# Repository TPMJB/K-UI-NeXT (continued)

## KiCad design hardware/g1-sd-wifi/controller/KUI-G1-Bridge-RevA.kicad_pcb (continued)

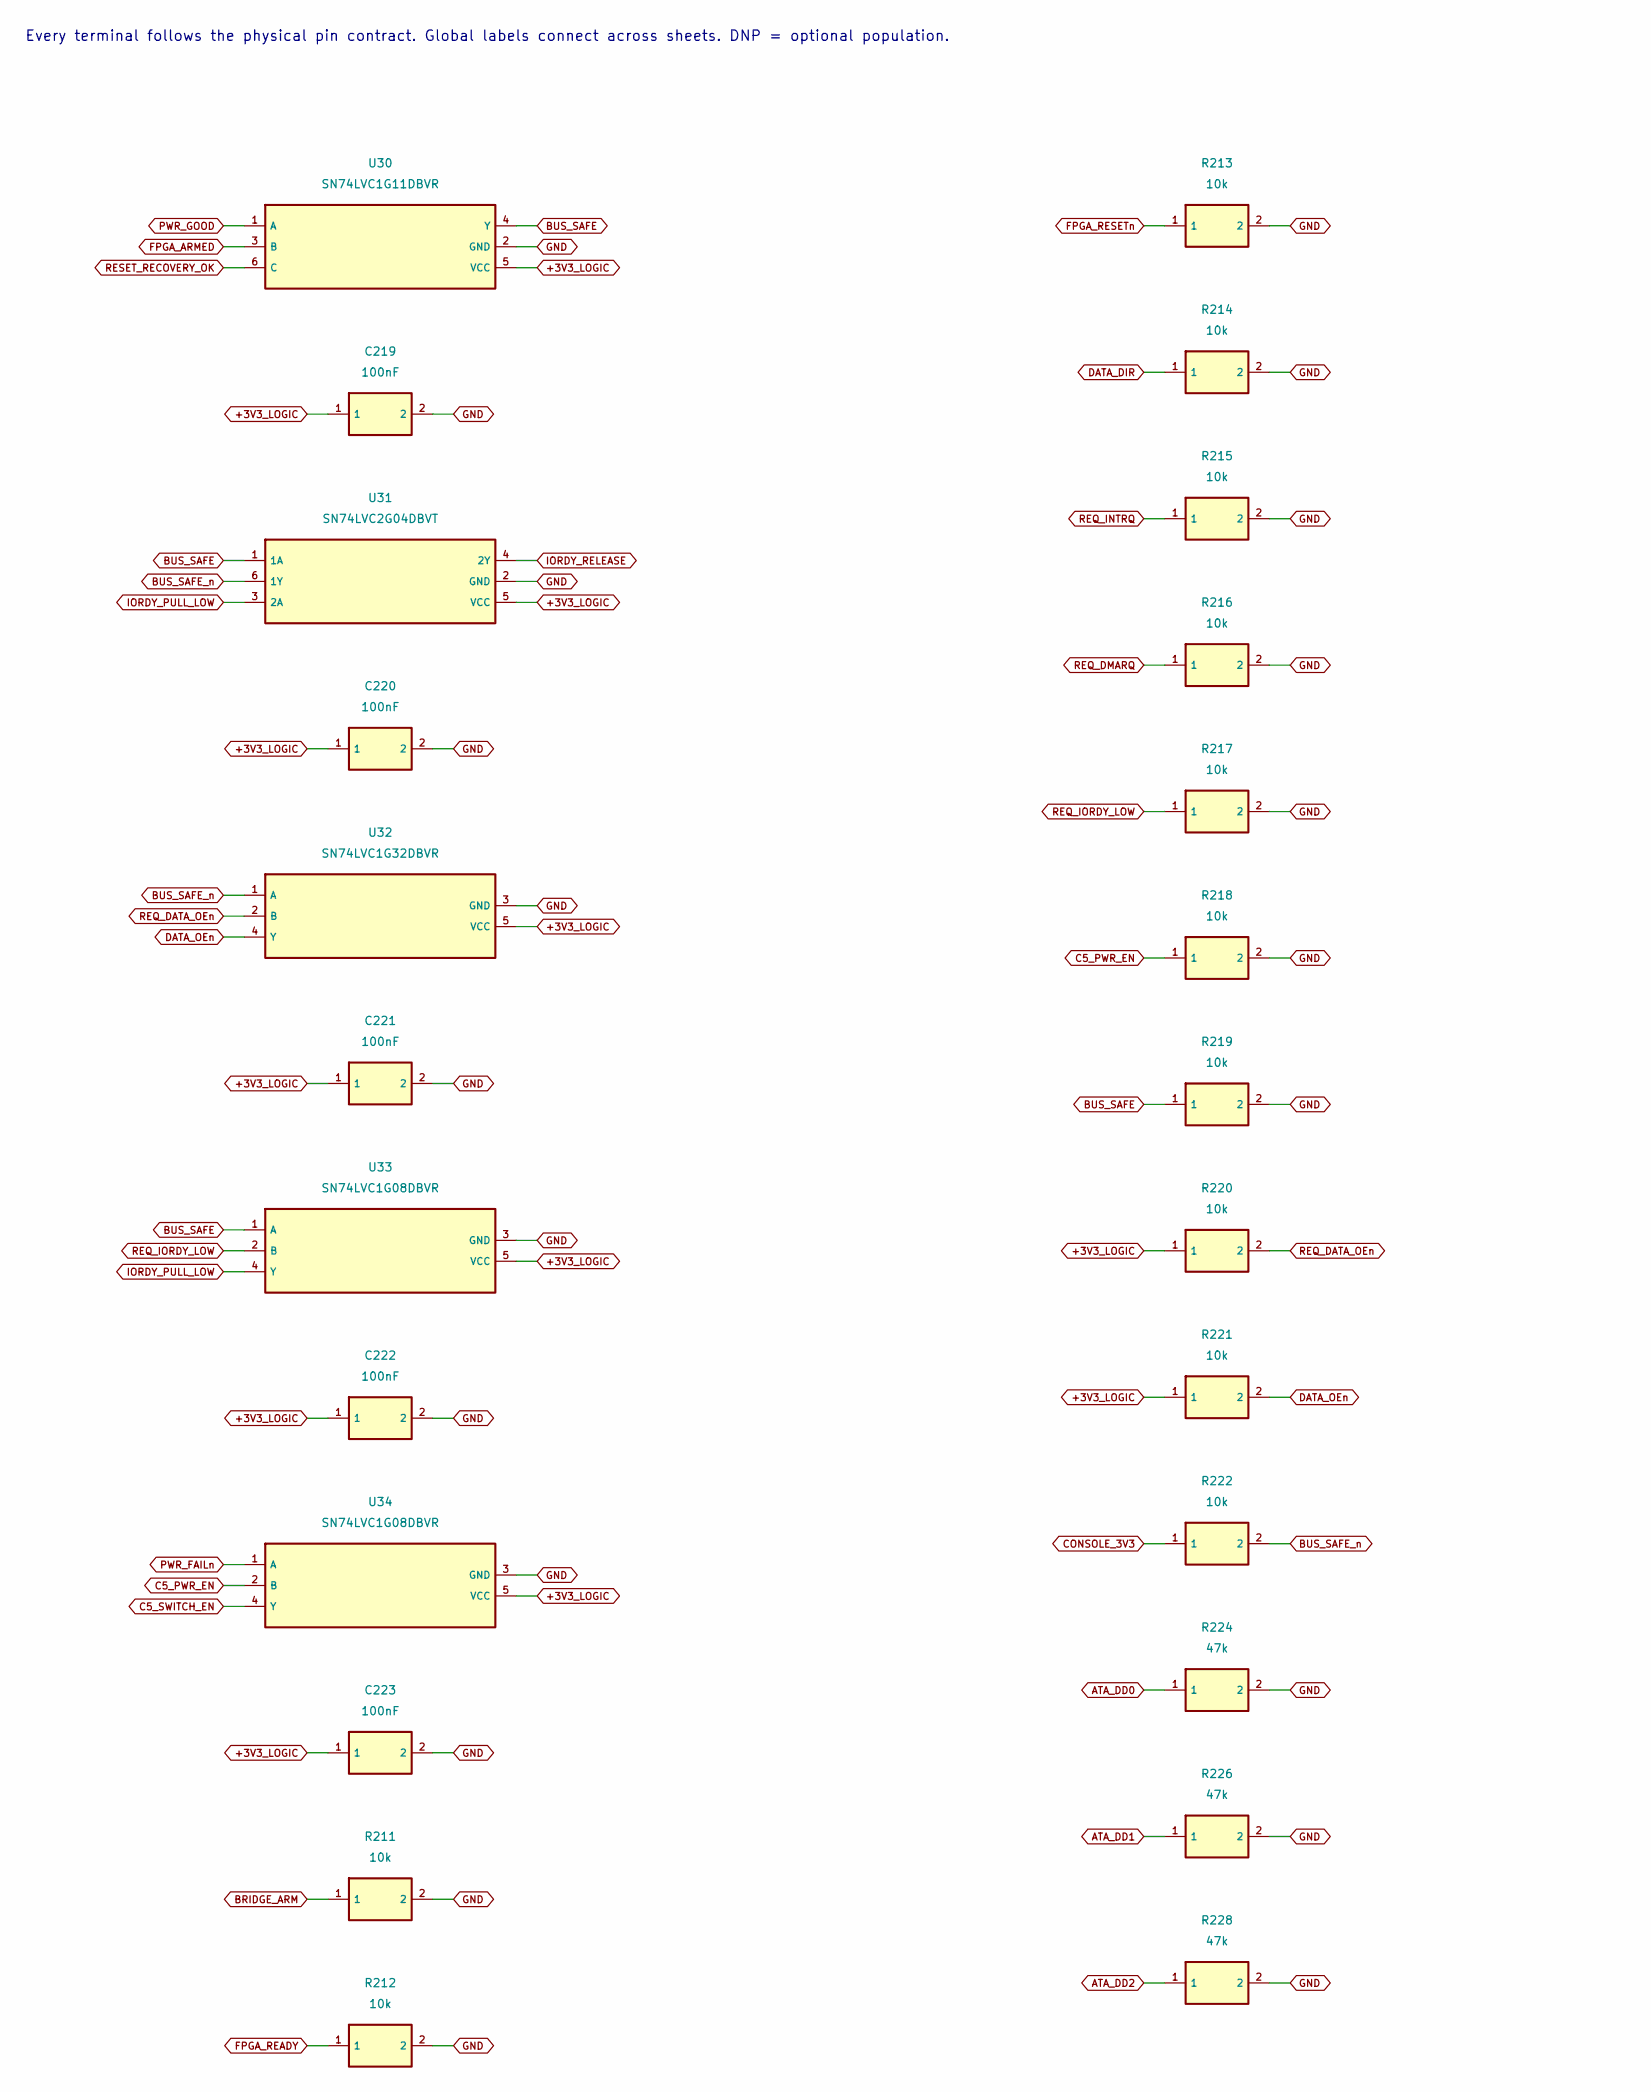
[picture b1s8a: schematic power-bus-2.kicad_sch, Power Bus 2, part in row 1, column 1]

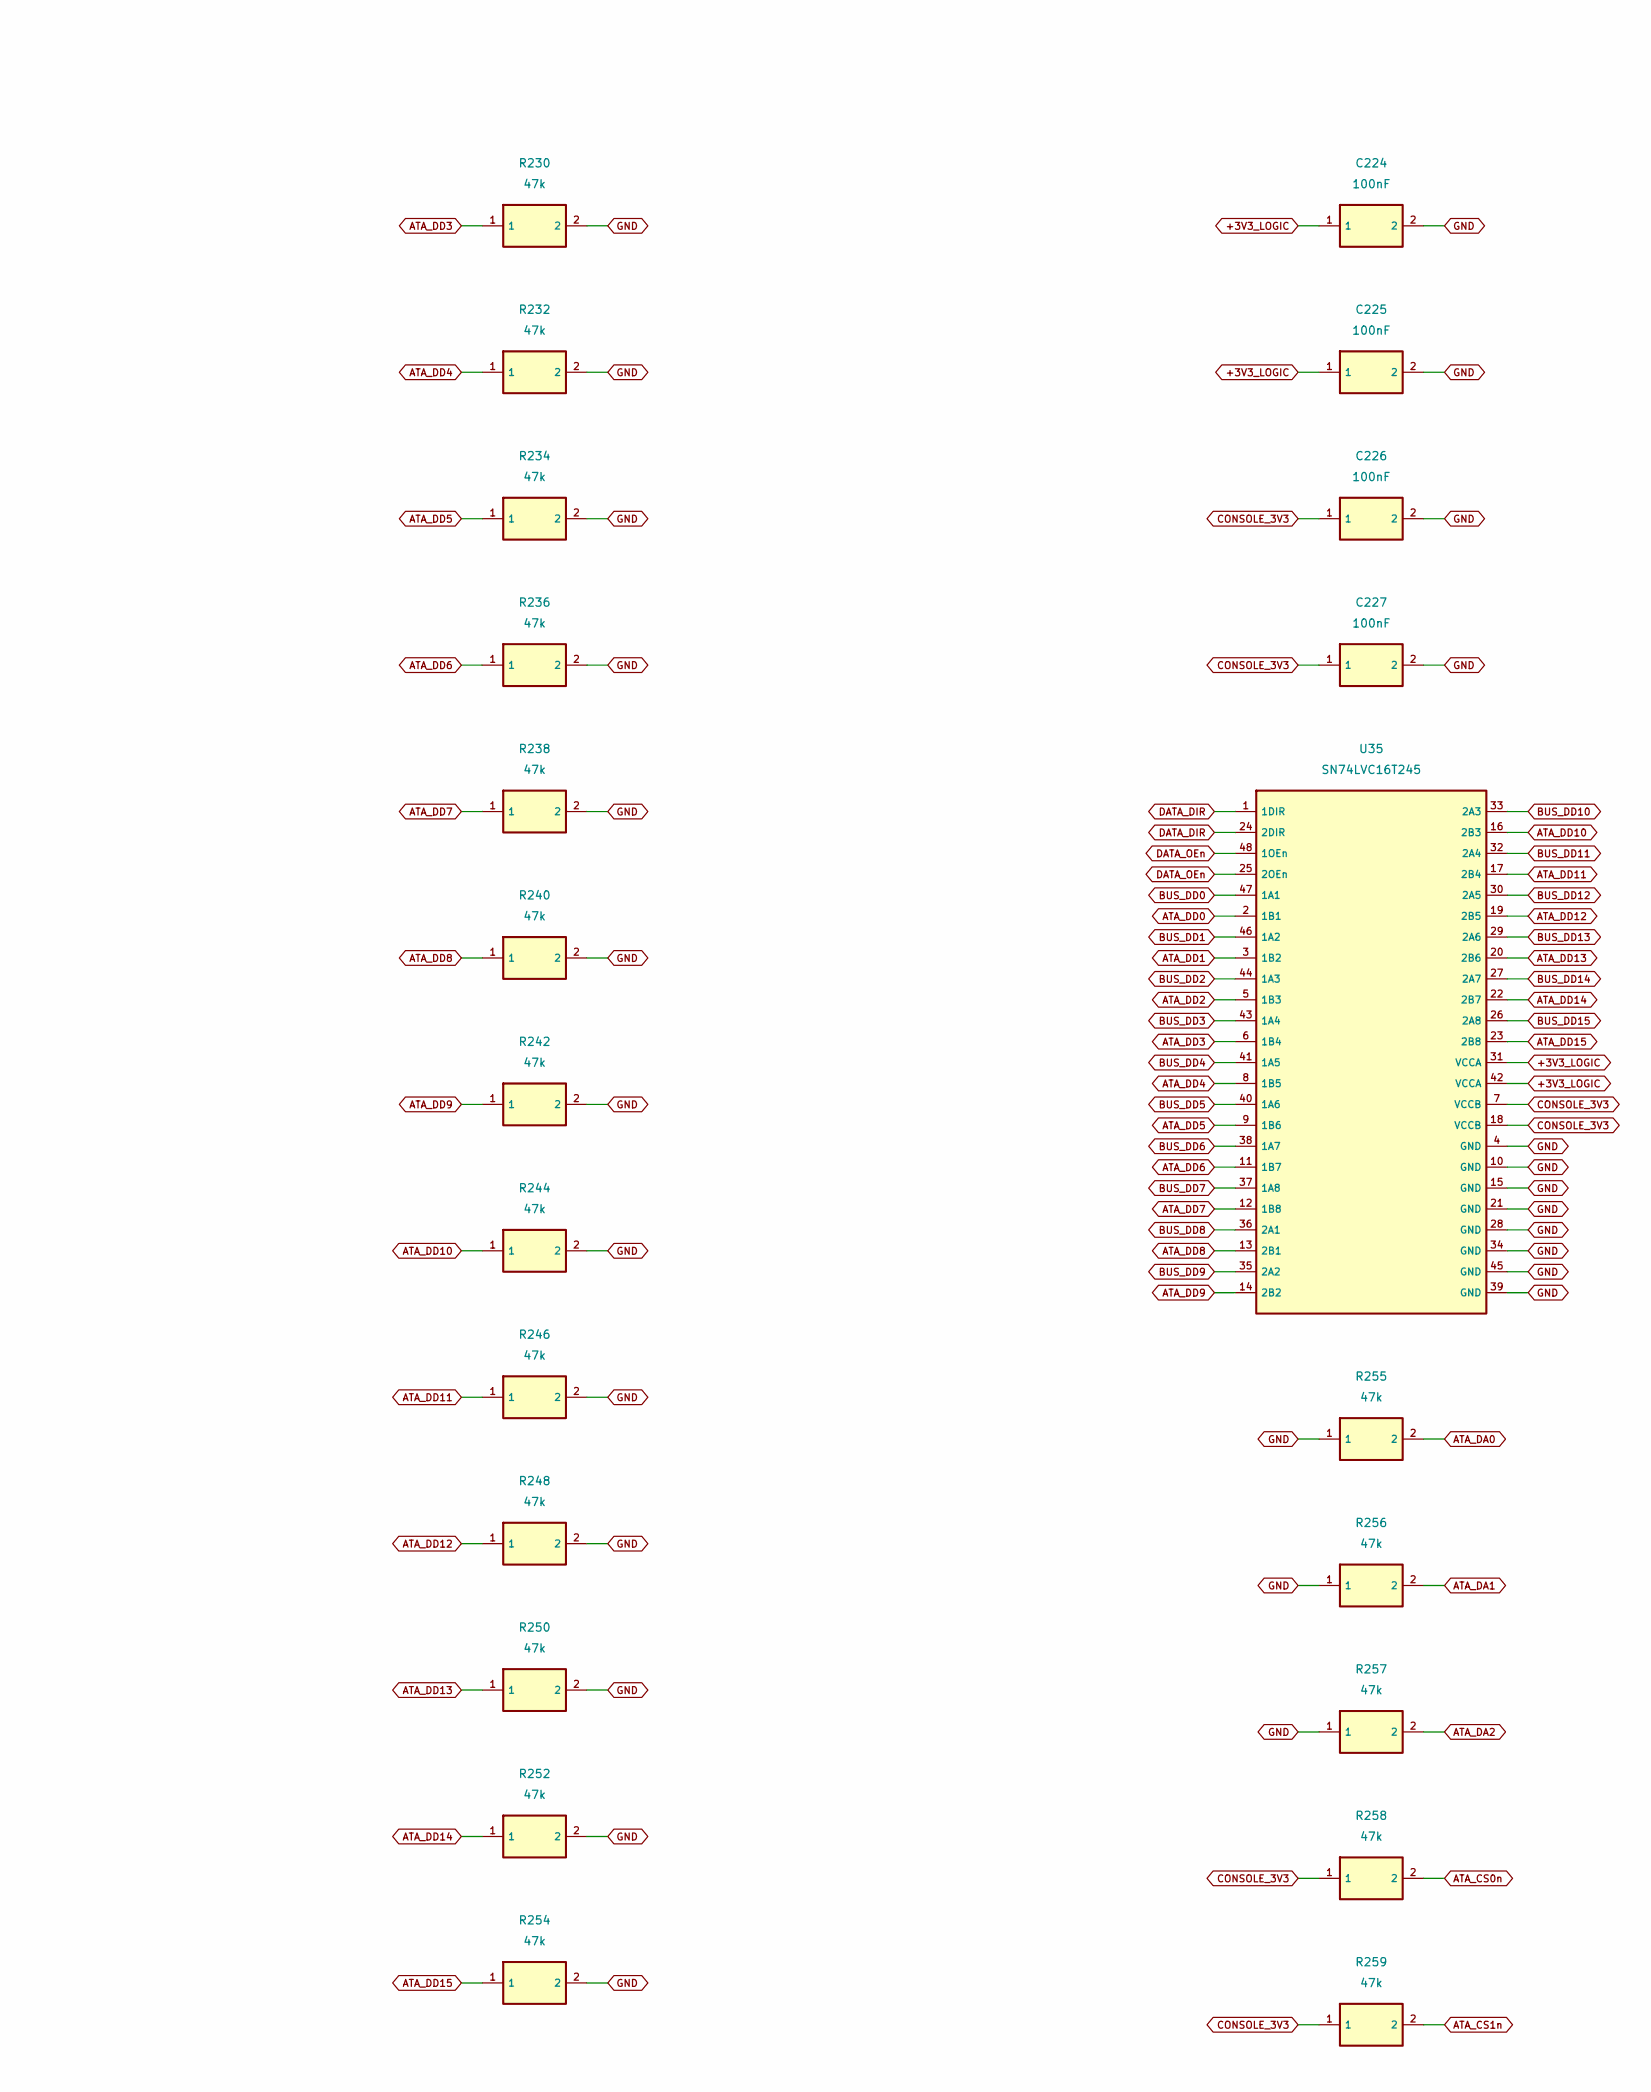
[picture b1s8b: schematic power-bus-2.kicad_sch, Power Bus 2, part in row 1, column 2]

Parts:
C219, C220, C221, C222, C223, C224, C225, C226, C227: 100nF; C_0402_1005Metric; MPN GRM155R71C104KA88D
R211, R212, R213, R214, R215, R216, R217, R218, R219, R220, R221, R222: 10k; R_0402_1005Metric; MPN RC0402FR-0710KL
R224, R226, R228, R230, R232, R234, R236, R238, R240, R242, R244, R246, R248, R250, R252, R254, R255, R256, R257, R258, R259: 47k; R_0402_1005Metric; MPN RC0402FR-0747KL
U30: SN74LVC1G11DBVR; SOT-23-6; MPN SN74LVC1G11DBVR
U31: SN74LVC2G04DBVT; SOT-23-6; MPN SN74LVC2G04DBVT; LCSC C2860342
U32: SN74LVC1G32DBVR; SOT-23-5; MPN SN74LVC1G32DBVR
U33, U34: SN74LVC1G08DBVR; SOT-23-5; MPN SN74LVC1G08DBVR
U35: SN74LVC16T245; TSSOP-48_6.1x12.5mm_P0.5mm; MPN SN74LVC16T245DGGR

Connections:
+3V3_LOGIC: C219.1, C220.1, C221.1, C222.1, C223.1, C224.1, C225.1, R220.1, R221.1, U30.5 (VCC), U31.5 (VCC), U32.5 (VCC), U33.5 (VCC), U34.5 (VCC), U35.31 (VCCA), U35.42 (VCCA); also elsewhere on the board
ATA_CS0n: R258.2; also elsewhere on the board
ATA_CS1n: R259.2; also elsewhere on the board
ATA_DA0: R255.2; also elsewhere on the board
ATA_DA1: R256.2; also elsewhere on the board
ATA_DA2: R257.2; also elsewhere on the board
ATA_DD0: R224.1, U35.2 (1B1); also elsewhere on the board
ATA_DD1: R226.1, U35.3 (1B2); also elsewhere on the board
ATA_DD2: R228.1, U35.5 (1B3); also elsewhere on the board
ATA_DD3: R230.1, U35.6 (1B4); also elsewhere on the board
ATA_DD4: R232.1, U35.8 (1B5); also elsewhere on the board
ATA_DD5: R234.1, U35.9 (1B6); also elsewhere on the board
ATA_DD6: R236.1, U35.11 (1B7); also elsewhere on the board
ATA_DD7: R238.1, U35.12 (1B8); also elsewhere on the board
ATA_DD8: R240.1, U35.13 (2B1); also elsewhere on the board
ATA_DD9: R242.1, U35.14 (2B2); also elsewhere on the board
ATA_DD10: R244.1, U35.16 (2B3); also elsewhere on the board
ATA_DD11: R246.1, U35.17 (2B4); also elsewhere on the board
ATA_DD12: R248.1, U35.19 (2B5); also elsewhere on the board
ATA_DD13: R250.1, U35.20 (2B6); also elsewhere on the board
ATA_DD14: R252.1, U35.22 (2B7); also elsewhere on the board
ATA_DD15: R254.1, U35.23 (2B8); also elsewhere on the board
BRIDGE_ARM: R211.1; also elsewhere on the board
BUS_DD0: U35.47 (1A1); also elsewhere on the board
BUS_DD1: U35.46 (1A2); also elsewhere on the board
BUS_DD2: U35.44 (1A3); also elsewhere on the board
BUS_DD3: U35.43 (1A4); also elsewhere on the board
BUS_DD4: U35.41 (1A5); also elsewhere on the board
BUS_DD5: U35.40 (1A6); also elsewhere on the board
BUS_DD6: U35.38 (1A7); also elsewhere on the board
BUS_DD7: U35.37 (1A8); also elsewhere on the board
BUS_DD8: U35.36 (2A1); also elsewhere on the board
BUS_DD9: U35.35 (2A2); also elsewhere on the board
BUS_DD10: U35.33 (2A3); also elsewhere on the board
BUS_DD11: U35.32 (2A4); also elsewhere on the board
BUS_DD12: U35.30 (2A5); also elsewhere on the board
BUS_DD13: U35.29 (2A6); also elsewhere on the board
BUS_DD14: U35.27 (2A7); also elsewhere on the board
BUS_DD15: U35.26 (2A8); also elsewhere on the board
BUS_SAFE: R219.1, U30.4 (Y), U31.1 (1A), U33.1 (A); also elsewhere on the board
BUS_SAFE_n: R222.2, U31.6 (1Y), U32.1 (A); also elsewhere on the board
C5_PWR_EN: R218.1, U34.2 (B); also elsewhere on the board
C5_SWITCH_EN: U34.4 (Y); also elsewhere on the board
CONSOLE_3V3: C226.1, C227.1, R222.1, R258.1, R259.1, U35.7 (VCCB), U35.18 (VCCB); also elsewhere on the board
DATA_DIR: R214.1, U35.1 (1DIR), U35.24 (2DIR); also elsewhere on the board
DATA_OEn: R221.2, U32.4 (Y), U35.25 (2OEn), U35.48 (1OEn); also elsewhere on the board
FPGA_ARMED: U30.3 (B); also elsewhere on the board
FPGA_READY: R212.1; also elsewhere on the board
FPGA_RESETn: R213.1; also elsewhere on the board
GND: C219.2, C220.2, C221.2, C222.2, C223.2, C224.2, C225.2, C226.2, C227.2, R211.2, R212.2, R213.2, R214.2, R215.2, R216.2, R217.2, R218.2, R219.2, R224.2, R226.2, R228.2, R230.2, R232.2, R234.2, R236.2, R238.2, R240.2, R242.2, R244.2, R246.2, R248.2, R250.2, R252.2, R254.2, R255.1, R256.1, R257.1, U30.2 (GND), U31.2 (GND), U32.3 (GND), U33.3 (GND), U34.3 (GND), U35.4 (GND), U35.10 (GND), U35.15 (GND), U35.21 (GND), U35.28 (GND), U35.34 (GND), U35.39 (GND), U35.45 (GND); also elsewhere on the board
IORDY_PULL_LOW: U31.3 (2A), U33.4 (Y)
IORDY_RELEASE: U31.4 (2Y); also elsewhere on the board
PWR_FAILn: U34.1 (A); also elsewhere on the board
PWR_GOOD: U30.1 (A); also elsewhere on the board
REQ_DATA_OEn: R220.2, U32.2 (B); also elsewhere on the board
REQ_DMARQ: R216.1; also elsewhere on the board
REQ_INTRQ: R215.1; also elsewhere on the board
REQ_IORDY_LOW: R217.1, U33.2 (B); also elsewhere on the board
RESET_RECOVERY_OK: U30.6 (C); also elsewhere on the board

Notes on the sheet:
Every terminal follows the physical pin contract. Global labels connect across sheets. DNP = optional population.

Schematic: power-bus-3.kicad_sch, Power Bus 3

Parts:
C228, C229, C230, C231, C232, C233, C234: 100nF; C_0402_1005Metric; MPN GRM155R71C104KA88D
C235, C236: 22uF; C_0805_2012Metric; MPN GRM21BR61A226ME51L
R260, R261, R262, R263: 47k; R_0402_1005Metric; MPN RC0402FR-0747KL
R264, R265, R266, R267, R268: 10k; R_0402_1005Metric; MPN RC0402FR-0710KL
R269: 100k; R_0402_1005Metric; MPN RC0402FR-07100KL
TP20: PWR_FAILn; TestPoint_Pad_D1.0mm; MPN PCB test point
TP21: PWR_GOOD; TestPoint_Pad_D1.0mm; MPN PCB test point
TP22: BUS_SAFE; TestPoint_Pad_D1.0mm; MPN PCB test point
TP23: DATA_OEn; TestPoint_Pad_D1.0mm; MPN PCB test point
TP24: +5V_HOLD; TestPoint_Pad_D1.0mm; MPN PCB test point
TP25: RESERVE_5V; TestPoint_Pad_D1.0mm; MPN PCB test point
TP26: CONSOLE_3V3; TestPoint_Pad_D1.0mm; MPN PCB test point
U36: SN74LVC244A host controls; TSSOP-20_4.4x6.5mm_P0.65mm; MPN SN74LVC244APWR
U37: SN74LVC1G17 host RESETn; SOT-23-5; MPN SN74LVC1G17DBVR
U38: SN74LVC1G125 qualified ATA_INTRQ; SOT-23-5; MPN SN74LVC1G125DBVR
U39: SN74LVC1G125 qualified ATA_DMARQ; SOT-23-5; MPN SN74LVC1G125DBVR
U70: SN74LVC1G07 open-drain IORDY; SOT-23-5; MPN SN74LVC1G07DBVR
U71: TPS22919 Wi-Fi input switch; SOT-363_SC-70-6; MPN TPS22919DCKR
U72, U73: SN74LVC1G32DBVR; SOT-23-5; MPN SN74LVC1G32DBVR

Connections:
+3V3_LOGIC: C228.1, C229.1, C230.1, C232.1, R264.1, R266.1, U36.20 (VCC), U37.5 (VCC), U72.5 (VCC), U73.5 (VCC); also elsewhere on the board
+5V_C5: C236.1, U71.5 (QOD), U71.6 (VOUT); also elsewhere on the board
+5V_HOLD: TP24.1; also elsewhere on the board
ATA_CS0n: U36.8 (1A4); also elsewhere on the board
ATA_CS1n: U36.11 (2A1); also elsewhere on the board
ATA_DA0: U36.2 (1A1); also elsewhere on the board
ATA_DA1: U36.4 (1A2); also elsewhere on the board
ATA_DA2: U36.6 (1A3); also elsewhere on the board
ATA_DIORn: R260.2, U36.13 (2A2); also elsewhere on the board
ATA_DIOWn: R261.2, U36.15 (2A3); also elsewhere on the board
ATA_DMACKn: R262.2, U36.17 (2A4); also elsewhere on the board
ATA_DMARQ: U39.4 (Y); also elsewhere on the board
ATA_INTRQ: U38.4 (Y); also elsewhere on the board
ATA_IORDY: U70.4 (Y); also elsewhere on the board
ATA_RESETn: R263.1, U37.2 (A); also elsewhere on the board
BUS_CS0n: U36.12 (1Y4); also elsewhere on the board
BUS_CS1n: U36.9 (2Y1); also elsewhere on the board
BUS_DA0: U36.18 (1Y1); also elsewhere on the board
BUS_DA1: U36.16 (1Y2); also elsewhere on the board
BUS_DA2: U36.14 (1Y3); also elsewhere on the board
BUS_DIORn: U36.7 (2Y2); also elsewhere on the board
BUS_DIOWn: U36.5 (2Y3); also elsewhere on the board
BUS_DMACKn: U36.3 (2Y4); also elsewhere on the board
BUS_RESETn: U37.4 (Y); also elsewhere on the board
BUS_SAFE: TP22.1; also elsewhere on the board
BUS_SAFE_n: U72.1 (A), U73.1 (A); also elsewhere on the board
C5_SWITCH_EN: R269.1, U71.3 (ON); also elsewhere on the board
CONSOLE_3V3: C231.1, C233.1, C234.1, R260.1, R261.1, R262.1, R265.1, R267.1, R268.1, TP26.1, U38.5 (VCC), U39.5 (VCC), U70.5 (VCC); also elsewhere on the board
DATA_OEn: TP23.1; also elsewhere on the board
DMARQ_OEn: R267.2, U39.1 (OEn), U73.4 (Y); also elsewhere on the board
GND: C228.2, C229.2, C230.2, C231.2, C232.2, C233.2, C234.2, C235.2, C236.2, R263.2, R269.2, U36.1 (1OEn), U36.10 (GND), U36.19 (2OEn), U37.3 (GND), U38.3 (GND), U39.3 (GND), U70.3 (GND), U71.2 (GND), U72.3 (GND), U73.3 (GND); also elsewhere on the board
INTRQ_OEn: R265.2, U38.1 (OEn), U72.4 (Y); also elsewhere on the board
IORDY_RELEASE: R268.2, U70.2 (A); also elsewhere on the board
PRIMARY_5V: C235.1, U71.1 (IN); also elsewhere on the board
PWR_FAILn: TP20.1; also elsewhere on the board
PWR_GOOD: TP21.1; also elsewhere on the board
REQ_DMARQ: U39.2 (A); also elsewhere on the board
REQ_DMARQ_OEn: R266.2, U73.2 (B); also elsewhere on the board
REQ_INTRQ: U38.2 (A); also elsewhere on the board
REQ_INTRQ_OEn: R264.2, U72.2 (B); also elsewhere on the board
RESERVE_5V: TP25.1; also elsewhere on the board

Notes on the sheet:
Every terminal follows the physical pin contract. Global labels connect across sheets. DNP = optional population.

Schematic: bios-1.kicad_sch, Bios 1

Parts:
C400, C402, C403, C404, C405, C406: 100nF; C_0603_1608Metric; MPN CC0603KRX7R9BB104; not fitted
C401: 4.7uF; C_0603_1608Metric; MPN GRM188R60J475KE19D; not fitted
J40: FH12-14S-0.5SH(55); Hirose_FH12-14S-0.5SH_1x14-1MP_P0.50mm_Horizontal; MPN FH12-14S-0.5SH(55); not fitted
J41: FH12-6S-0.5SH(55); Hirose_FH12-6S-0.5SH_1x06-1MP_P0.50mm_Horizontal; MPN FH12-6S-0.5SH(55); not fitted
JP40: PROGRAM ARM - normally OPEN; SolderJumper-2_P1.3mm_Open_RoundedPad1.0x1.5mm; MPN PCB_SOLDER_BRIDGE; not fitted
R400, R401, R402, R403, R404, R405, R406, R407, R408, R412, R413, R414: 10k; R_0603_1608Metric; MPN RC0603FR-0710KL; not fitted
R409: 10k; R_0603_1608Metric; MPN RC0603FR-0710KL
R410: 1k; R_0402_1005Metric; MPN RC0402FR-071KL
R411: 100k; R_0603_1608Metric; MPN RC0603FR-07100KL; not fitted
SW40: STOCK_RECOVERY / CUSTOM (OFFBOARD); MPN 7201SYZBE; not fitted
TP40: NOR_RY_BY; TestPoint_Pad_D1.0mm; MPN PCB_TEST_PAD; not fitted
U40: MX29LV640ETTI-70G x8 / 4 x 2MiB; TSOP-I-48_18.4x12mm_P0.5mm; MPN MX29LV640ETTI-70G; not fitted
U41: SN74LVC2G125 bank-domain buffer; SOT-23-8; MPN SN74LVC2G125DCTR; not fitted
U42: SN74LVC1G11 write-authorize AND; SOT-23-6; MPN SN74LVC1G11DBVR; not fitted
U43: SN74LVC1G04 write-block inverter; SOT-23-5; MPN SN74LVC1G04DBVR; not fitted
U44: SN74LVC1G332 NOR WE qualifier; SOT-23-6; MPN SN74LVC1G332DBVR; not fitted
U45: TLV803EB29 console-rail NOR reset; SOT-23; MPN TLV803EB29DBZR; not fitted

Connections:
ATA_DA0: U40.18 (A7); also elsewhere on the board
ATA_DA1: U40.8 (A8); also elsewhere on the board
ATA_DA2: U40.7 (A9); also elsewhere on the board
ATA_DD0: U40.29 (DQ0); also elsewhere on the board
ATA_DD1: U40.31 (DQ1); also elsewhere on the board
ATA_DD2: U40.33 (DQ2); also elsewhere on the board
ATA_DD3: U40.35 (DQ3); also elsewhere on the board
ATA_DD4: U40.38 (DQ4); also elsewhere on the board
ATA_DD5: U40.40 (DQ5); also elsewhere on the board
ATA_DD6: U40.42 (DQ6); also elsewhere on the board
ATA_DD7: U40.44 (DQ7); also elsewhere on the board
ATA_DD8: U40.45 (DQ15/A-1); also elsewhere on the board
ATA_DD9: U40.25 (A0); also elsewhere on the board
ATA_DD10: U40.24 (A1); also elsewhere on the board
ATA_DD11: U40.23 (A2); also elsewhere on the board
ATA_DD12: U40.22 (A3); also elsewhere on the board
ATA_DD13: U40.21 (A4); also elsewhere on the board
ATA_DD14: U40.20 (A5); also elsewhere on the board
ATA_DD15: U40.19 (A6); also elsewhere on the board
ATA_DIORn: U40.28 (OE#); also elsewhere on the board
ATA_DIOWn: U44.1 (A); also elsewhere on the board
BIOS_BANK0: R403.1, U41.2 (1A); also elsewhere on the board
BIOS_BANK1: R404.1, U41.5 (2A); also elsewhere on the board
BIOS_FLASH_ARMED: JP40.2 (ARM), R411.1, U42.3 (B)
BIOS_NOR_BANK0: R405.1, U40.10 (A20), U41.6 (1Y)
BIOS_NOR_BANK1: R406.1, U40.13 (A21), U41.3 (2Y)
BIOS_NOR_CEn: J41.3 (CUSTOM_NOR_CE), R400.1, SW40.3 (CUSTOM_NOR_CE), U40.26 (CE#), U44.3 (B)
BIOS_NOR_RBYn: R413.1, TP40.1, U40.15 (RY/BY#)
BIOS_NOR_RESETn: JP40.1 (RAIL_GOOD), R412.1, U40.12 (RESET#), U45.2 (RESET#)
BIOS_NOR_WEn: R402.1, U40.11 (WE#), U44.4 (Y)
BIOS_RECOVERYn: J41.5 (RECOVERY_INTERLOCK_C), R409.1, R410.1, SW40.5 (RECOVERY_INTERLOCK_C), U42.1 (A); also elsewhere on the board
BIOS_WP_ACC: R414.1, U40.14 (WP#/ACC)
BIOS_WRITE_ALLOWED: R408.1, U42.4 (Y), U43.2 (A)
BIOS_WRITE_BLOCKED: U43.4 (Y), U44.6 (C)
BIOS_WR_EN: R407.1, U42.6 (C); also elsewhere on the board
CONSOLE_3V3: C400.1, C401.1, C402.1, C403.1, C404.1, C405.1, C406.1, J41.6 (CUSTOM_3V3), R400.2, R401.2, R402.2, R410.2, R412.2, R413.2, R414.2, SW40.6 (CUSTOM_3V3), U40.37 (VCC), U41.8 (VCC), U42.5 (VCC), U43.5 (VCC), U44.5 (VCC), U45.3 (VDD); also elsewhere on the board
GND: C400.2, C401.2, C402.2, C403.2, C404.2, C405.2, C406.2, J40.13 (GND), J40.14 (GND), J40.MP (MOUNTING_PADS), J41.4 (STOCK_RECOVERY_GND), J41.MP (MOUNTING_PADS), R403.2, R404.2, R405.2, R406.2, R407.2, R408.2, R409.2, R411.2, SW40.4 (STOCK_RECOVERY_GND), U40.27 (GND), U40.46 (GND), U40.47 (BYTE#), U41.1 (1OE#), U41.4 (GND), U41.7 (2OE#), U42.2 (GND), U43.3 (GND), U44.2 (GND), U45.1 (GND); also elsewhere on the board
ROM_A10: J40.1 (ROM_A10), U40.6 (A10)
ROM_A11: J40.2 (ROM_A11), U40.5 (A11)
ROM_A12: J40.3 (ROM_A12), U40.4 (A12)
ROM_A13: J40.4 (ROM_A13), U40.3 (A13)
ROM_A14: J40.5 (ROM_A14), U40.2 (A14)
ROM_A15: J40.6 (ROM_A15), U40.1 (A15)
ROM_A16: J40.7 (ROM_A16), U40.48 (A16)
ROM_A17: J40.8 (ROM_A17), U40.17 (A17)
ROM_A18: J40.9 (ROM_A18), U40.16 (A18)
ROM_A19: J40.10 (ROM_A19), U40.9 (A19)
ROM_CEn: J40.11 (HOLLY_ROM_CE_PAD), J41.2 (HOLLY_ROM_CE_COMMON), SW40.2 (HOLLY_ROM_CE_COMMON)
STOCK_CEn: J40.12 (ISOLATED_STOCK_CE_LE), J41.1 (STOCK_CE), R401.1, SW40.1 (STOCK_CE)

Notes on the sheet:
Every terminal follows the physical pin contract. Global labels connect across sheets. DNP = optional population.
DNP / BIOS_OPTION

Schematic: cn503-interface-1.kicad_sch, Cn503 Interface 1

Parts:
J50, J51: FH12-20S-0.5SH(55); Hirose_FH12-20S-0.5SH_1x20-1MP_P0.50mm_Horizontal; MPN FH12-20S-0.5SH(55)

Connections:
ATA_CS0n: J50.19 (A20); also elsewhere on the board
ATA_CS1n: J51.2 (B20); also elsewhere on the board
ATA_DA0: J50.18 (A19); also elsewhere on the board
ATA_DA1: J51.5 (B17); also elsewhere on the board
ATA_DA2: J51.3 (B19); also elsewhere on the board
ATA_DD0: J51.11 (B11); also elsewhere on the board
ATA_DD1: J50.11 (A11); also elsewhere on the board
ATA_DD2: J51.13 (B9); also elsewhere on the board
ATA_DD3: J50.9 (A9); also elsewhere on the board
ATA_DD4: J51.16 (B6); also elsewhere on the board
ATA_DD5: J50.6 (A6); also elsewhere on the board
ATA_DD6: J51.18 (B4); also elsewhere on the board
ATA_DD7: J50.4 (A4); also elsewhere on the board
ATA_DD8: J50.5 (A5); also elsewhere on the board
ATA_DD9: J51.17 (B5); also elsewhere on the board
ATA_DD10: J50.7 (A7); also elsewhere on the board
ATA_DD11: J51.15 (B7); also elsewhere on the board
ATA_DD12: J50.10 (A10); also elsewhere on the board
ATA_DD13: J51.12 (B10); also elsewhere on the board
ATA_DD14: J50.12 (A12); also elsewhere on the board
ATA_DD15: J51.10 (B12); also elsewhere on the board
ATA_DIORn: J50.15 (A15); also elsewhere on the board
ATA_DIOWn: J51.8 (B14); also elsewhere on the board
ATA_DMACKn: J50.16 (A16); also elsewhere on the board
ATA_DMARQ: J50.14 (A14); also elsewhere on the board
ATA_INTRQ: J51.6 (B16); also elsewhere on the board
ATA_IORDY: J51.7 (B15); also elsewhere on the board
ATA_RESETn: J50.2 (A2); also elsewhere on the board
CONSOLE_3V3_FLEX: J51.20 (B1); also elsewhere on the board
GND: J50.8 (A8), J50.13 (A13), J50.17 (A18), J50.20 (A21), J50.MP (shield_anchor), J51.1 (B21), J51.4 (B18), J51.9 (B13), J51.14 (B8), J51.MP (shield_anchor); also elsewhere on the board

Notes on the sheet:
Every terminal follows the physical pin contract. Global labels connect across sheets. DNP = optional population.

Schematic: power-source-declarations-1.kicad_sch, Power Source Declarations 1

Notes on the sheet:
Every terminal follows the physical pin contract. Global labels connect across sheets. DNP = optional population.

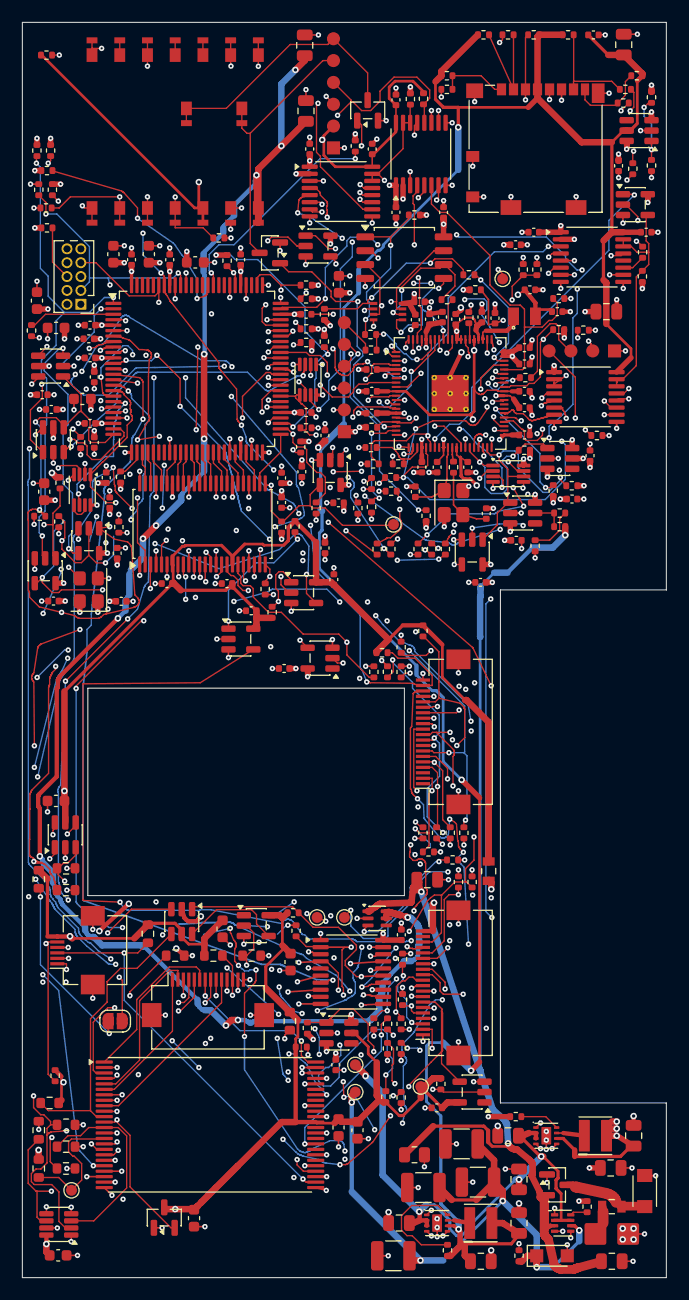
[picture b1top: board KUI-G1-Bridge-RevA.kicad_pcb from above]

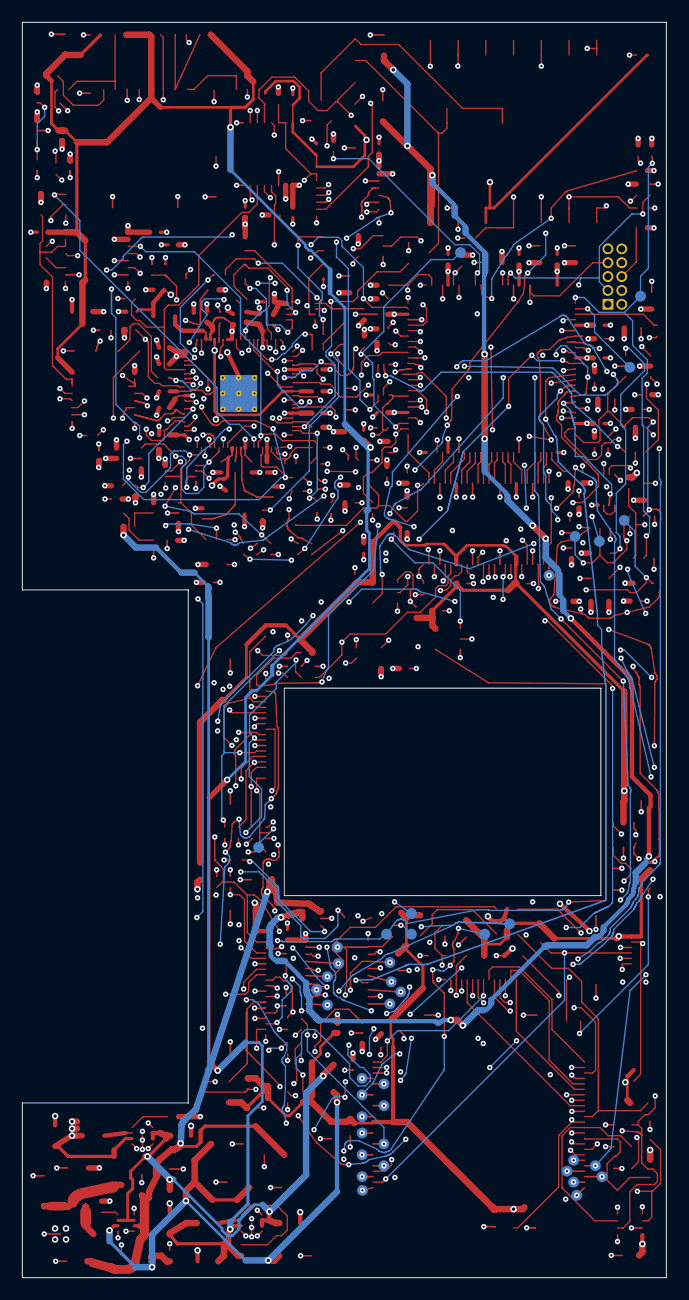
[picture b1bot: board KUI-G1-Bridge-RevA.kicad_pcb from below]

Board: 6 copper layers, 59.0 x 115.0 mm, 356 parts (39 on the bottom side), 230 nets.

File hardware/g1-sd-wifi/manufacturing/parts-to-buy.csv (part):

mpn,manufacturer,description,electrical_spec,physical_package,height_max_mm,footprint,qty_base,qty_bios_variant,qty_reserve_variant,qty_bios_and_reserve_variant,qty_base_psram_dnp_variant,qty_bios_psram_dnp_variant,qty_reserve_psram_dnp_variant,qty_bios_and_reserve_psram_dnp_variant,refs_base,refs_bios_only,refs_reserve_only,refs_base_only,refs_psram_only,refs_all,assembly_method,lcsc_code,sourcing_status,supplier_identity_url,jlc_assembly_status,jlc_assembly_url,jlc_pcba_type,jlc_fixture_notice,manufacturer_source_urls,spec_review_status,notes
0467.500NR,Littelfuse,0.5A fast fuse,"0.5-A fast-acting fuse; 32 V AC/DC; 50-A interrupt at 32 V; nominal cold resistance 0.187 ohm, melting I2t 0.0087 A2s","Littelfuse 467-series 0603/1608 fuse, body 1.60 +/-0.102 x 0.813 +/-0.076 mm, coated height 0.432 mm maximum; 0.5 mm conservative CAD budget",0.5,KUI_Footprints:Littelfuse_467_0603_Recommended,1,1,1,1,1,1,1,1,F21,,,,,F21,PCB SMT; assembler acceptance pending,C206990,catalog_identity_verified_assembly_pending,https://jlcpcb.com/partdetail/Littelfuse-0467500NR/C206990,jlc_smt_catalog_verified_order_acceptance_pending,https://jlcpcb.com/partdetail/Littelfuse-0467500NR/C206990,Economic and Standard,,https://www.littelfuse.com/assetdocs/fuse-467-datasheet?asse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,"Exact manufacturer electrical specification, mechanical dimensions, recommended land drawing and exact JLC catalog identity reviewed; native matching, assembly process and circuit fault/thermal qualification remain pending.","Exact NR suffix retained; NRHF is not selected. Manufacturer p3 reflow land: X 0.762/Y 1.09 mm pads at X 1.778 mm center pitch, X 2.54 mm overall. 1.02 mm labels rounded inner gap, not pad length. Manufacturer standard 25% continuous-current derating and temperature curve apply; F21/contact thermal coordination and voltage drop still require bench qualification."
046701.5NR,Littelfuse,1.5A fast fuse,1.5A fast fuse,"Littelfuse 467-series SMT fuse, 0603 imperial / 1608 metric",0.5,KUI_Footprints:Littelfuse_467_0603_Recommended,1,1,1,1,1,1,1,1,F20,,,,,F20,PCB SMT; assembler acceptance pending,C99559,catalog_identity_verified_assembly_pending,https://www.lcsc.com/product-detail/C99559.html,jlc_smt_catalog_verified_order_acceptance_pending,https://jlcpcb.com/partdetail/Littelfuse-0467015NR/C99559,Economic and Standard,,https://www.littelfuse.com/assetdocs/fuse-467-datasheet?asse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,Exact circuit MPN selected; procurement and operating qualification pending,"Exact NR suffix retained; NRHF is not selected. Manufacturer 467 p3 reflow land is now reproduced: X 0.762/Y 1.09 mm pads at X 1.778 mm center pitch, X 2.54 mm overall. Coated height 0.432 mm maximum; CAD budget 0.5 mm. Fuse/TVS fault clearing, inrush, thermal and reflow qualification remain pending."
100010048,Seeed Studio,XIAO ESP32-C5 USB removed,Seeed Studio XIAO ESP32C5 assembled radio module,"Seeed Studio XIAO ESP32C5 module, 21 x 17.8 mm; modified manual installation",0,,1,1,1,1,1,1,1,1,U206,,,,,U206,Manual offboard installation; excluded from carrier SMT placement,,sourcing_pending,,manual_purchase_not_carrier_smt,,,,https://www.seeedstudio.com/Seeed-Studio-XIAO-ESP32C5-p-6609.html | https://files.seeedstudio.com/wiki/XIAO_ESP32C5/res/Seeed_St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 | https://wiki.seeedstudio.com/xiao_esp32c5_wifi_usage/,Official maker SKU/package and board connection sources reviewed; modified-module qualification pending,"Manual module purchase. Remove USB connector and factory header protrusions according to fixture plan; no battery. Underside recovery pads use spring contacts. Removal/height/RF/mechanical verification pending. Manufacturer Wi-Fi instructions confirm a supplied external FPC antenna and U.FL connection. Use that included antenna outside the metal shield; installed cable route, bend/strain relief and dual-band RF qualification remain open. No separate unverified antenna purchase is added."
1040310811,Molex,microSD push-pull 1.42mm,microSD push-pull 1.42mm,"Molex 104031-0811 SMT microSD socket, 1.42 mm maximum height",0,Connector_Card:microSD_HC_Molex_104031-0811,1,1,1,1,1,1,1,1,J201,,,,,J201,PCB SMT; assembler acceptance pending,C585350,catalog_identity_verified_assembly_pending,https://www.lcsc.com/product-detail/C585350.html,jlc_smt_catalog_verified_order_acceptance_pending,https://jlcpcb.com/partdetail/MOLEX-1040310811/C585350,Economic and Standard,,https://www.molex.com/content/dam/molex/molex-dot-com/produc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 | https://www.molex.com/en-us/products/part-detail/1040310811,Exact circuit MPN selected; procurement and operating qualification pending,
"2N7002,215",Nexperia,C5 recovery pull-down,"Nexperia 2N7002 N-channel MOSFET, SOT23, tape code 215",SOT-23,0,Package_TO_SOT_SMD:SOT-23,2,2,2,2,2,2,2,2,"Q201,Q202",,,,,"Q201,Q202",PCB SMT; assembler acceptance pending,C65189,catalog_identity_verified_assembly_pending,https://www.lcsc.com/product-detail/C65189.html,jlc_smt_catalog_verified_order_acceptance_pending,"https://jlcpcb.com/partdetail/2N7002,215/C65189",Economic and Standard,,https://assets.nexperia.com/documents/data-sheet/2N7002.pdf,Manufacturer exact ordering code and physical pinout reviewed; circuit bench qualification pending,"Exact Nexperia part, gate1/source2/drain3. C5 recovery sink only; logic-level pull-down behavior at actual MCU drive must be bench checked."
7201SYZBE,C&K,STOCK_RECOVERY / CUSTOM (OFFBOARD),Gold-contact DPDT ON-ON physical stock/custom selector,"C&K 7000-series DPDT ON-ON panel toggle, offboard solder-lug termination",0,,0,1,0,1,0,1,0,1,,SW40,,,,SW40,Manual offboard installation; excluded from carrier SMT placement,,sourcing_pending,,manual_purchase_not_carrier_smt,,,,https://www.ckswitches.com/media/1394/7000toggle.pdf,Exact circuit MPN selected; procurement and operating qualification pending,Optional offboard installation; always change with whole console powered off. Stock CE path is physical and independent of MCU/FPGA. Remove R410 before populated selector connection.
ABM8-272-T3,Abracon,12MHz,"12 MHz crystal, CL10 pF, 3.2 x 2.5 x 0.8 mm, four pad",Crystal SMD 3225-4Pin 3.2x2.5mm,0,Crystal:Crystal_SMD_3225-4Pin_3.2x2.5mm,1,1,1,1,1,1,1,1,X201,,,,,X201,PCB SMT; assembler acceptance pending,C20625731,catalog_identity_verified_assembly_pending,https://www.lcsc.com/product-detail/C20625731.html,jlc_smt_catalog_verified_order_acceptance_pending,https://jlcpcb.com/partdetail/AbraconLLC-ABM8_272T3/C20625731,Economic and Standard,,https://pip-assets.raspberrypi.com/categories/1214-rp2350/do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 | https://datasheet.lcsc.com/datasheet/pdf/d5520a242c89eeaef42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,Manufacturer ABM8-272-T3 drawing and exact supplier nominal/package reviewed; oscillator margin qualification pending,
AOTA-B201610S3R3-101-T,Abracon,3.3uH,3.3 uH +/-20%; DCR 115 mOhm typical / 140 mOhm maximum; marked winding orientation,"Marked shielded SMT inductor, 2.0 x 1.6 x 1.0 mm",0,KUI_Footprints:AOTA-B201610S3R3-101-T,1,1,1,1,1,1,1,1,L201,,,,,L201,PCB SMT; assembler acceptance pending,C42411119,catalog_identity_verified_assembly_pending,https://www.lcsc.com/product-detail/C42411119.html,jlc_smt_catalog_verified_order_acceptance_pending,https://jlcpcb.com/partdetail/AbraconLlc-AOTA_B201610S3R3_10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,Economic and Standard,,https://abracon.com/datasheets/AOTA-B201610S3R3-101-T.pdf,Manufacturer electrical/package table reviewed; RP235x-approved part; operating qualification pending,Preserve RP235x reference winding polarity. Isat table lists 2.8 A typical and 2.4 A in Max column (30% L drop); Irms 2.3 A typical and 2.1 A in Max column (40 C rise). These labels are not a guaranteed minimum-current claim. Catalog availability is not reserved.
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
